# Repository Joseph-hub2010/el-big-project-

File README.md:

# El-big-project  
In this dearly week, we officially recognise a new project , a new experience and a new dream of becoming Great cooperators for 1 big project which is 🥁🥁🥁🥁🥁🥁🥁🥁🥁🥁    Steering car !!!
We believe , we do , we will.  
BY Joseph.

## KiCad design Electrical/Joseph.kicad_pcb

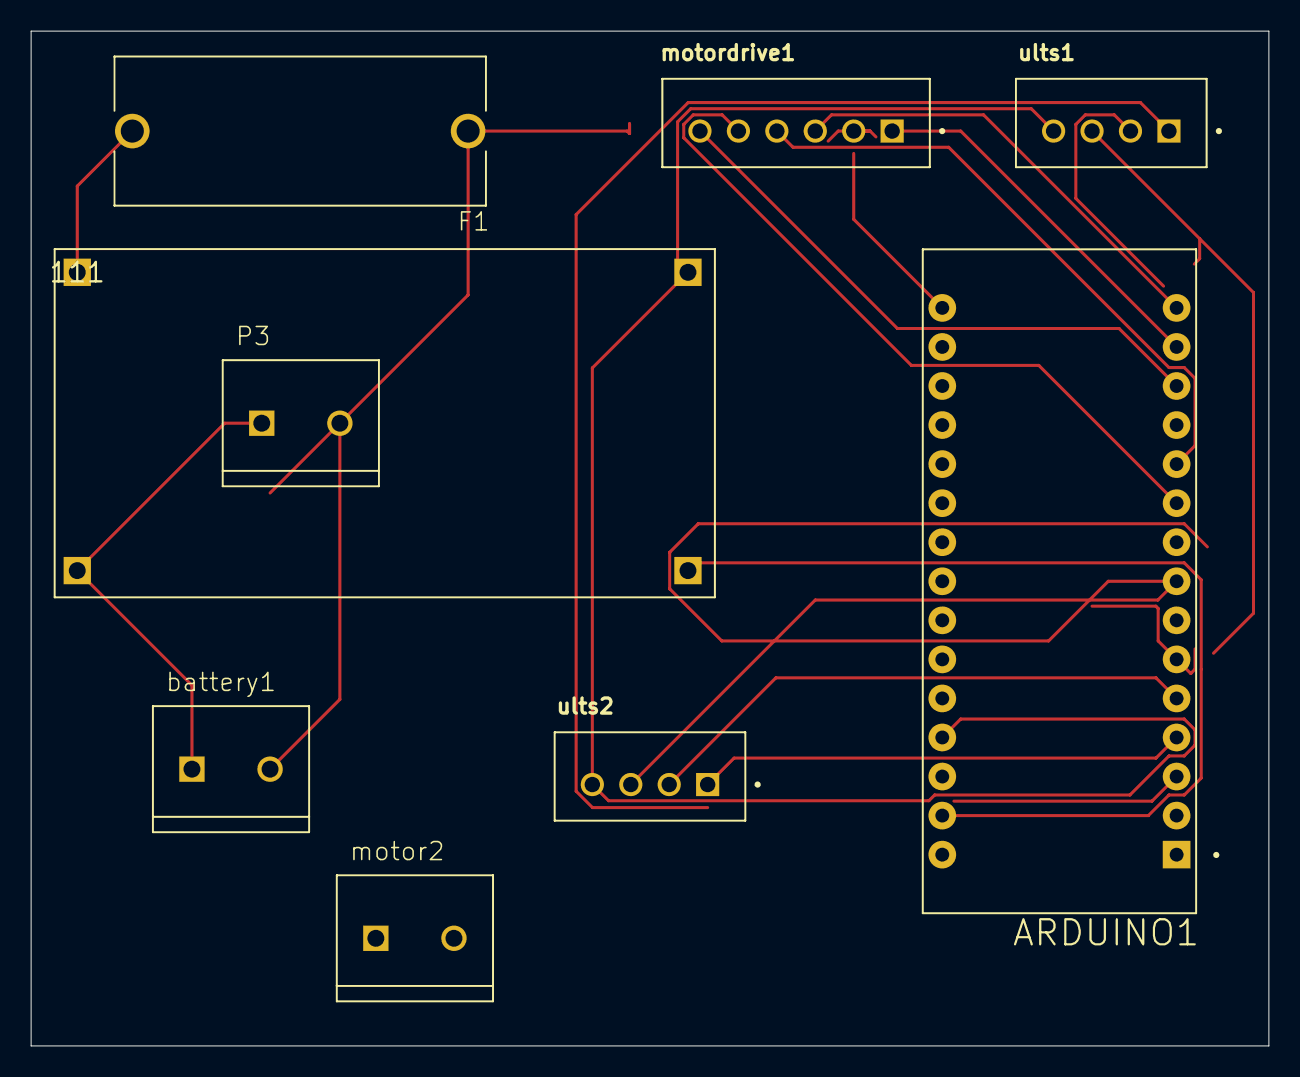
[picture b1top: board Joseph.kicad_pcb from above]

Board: 2 copper layers, 80.5 x 66.0 mm, 9 parts (0 on the bottom side), 16 nets.

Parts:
111: LM2596
ARDUINO1: SHIELD_ARDUINO_NANO
F1: FUSE_4527
P3: TE_282837-2
battery1: TE_282837-2
motor2: TE_282837-2
motordrive1: JST_B6B-XH-A(LF)(SN)
ults1, ults2: JST_B4B-XH-A(LF)(SN)

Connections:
+5V: 111.OUT+, ARDUINO1.27 (+5V), ults1.4, ults2.4
/ENA: ARDUINO1.13 (D10), motordrive1.6
/ENB: ARDUINO1.14 (D11/MOSI), motordrive1.1
/IN1: ARDUINO1.10 (D7), motordrive1.5
/IN2: ARDUINO1.11 (D8), motordrive1.4
/IN3: ARDUINO1.15 (D12/MISO), motordrive1.3
/IN4: ARDUINO1.16 (D13/SCK), motordrive1.2
/d2: ARDUINO1.5 (D2), ults2.2
/d3: ARDUINO1.6 (D3), ults1.3
/d4: ARDUINO1.7 (D4), ults1.2
/d5: ARDUINO1.8 (D5), ults2.3
GND: 111.OUT-, ARDUINO1.4 (COM/GND), ARDUINO1.29 (COM/GND), ults1.1, ults2.1
unnamed: 111.IN+, F1.2
unnamed: 111.IN-, P3.1, battery1.1
unnamed: ARDUINO1.3 (RESET), ARDUINO1.28 (RESET)
unnamed: F1.1, P3.2, battery1.2
